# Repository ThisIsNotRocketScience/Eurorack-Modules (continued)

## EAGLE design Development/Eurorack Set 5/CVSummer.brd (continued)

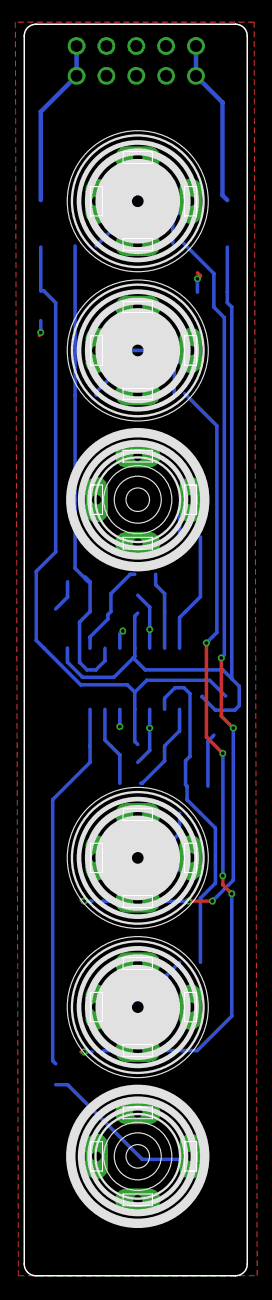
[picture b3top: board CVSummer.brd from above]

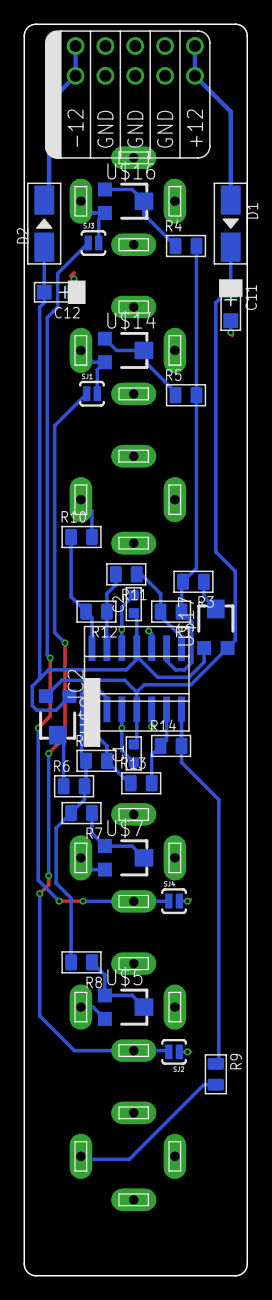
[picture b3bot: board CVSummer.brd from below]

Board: 2 copper layers, 19.0 x 106.5 mm, 39 parts (32 on the bottom side), 27 nets.

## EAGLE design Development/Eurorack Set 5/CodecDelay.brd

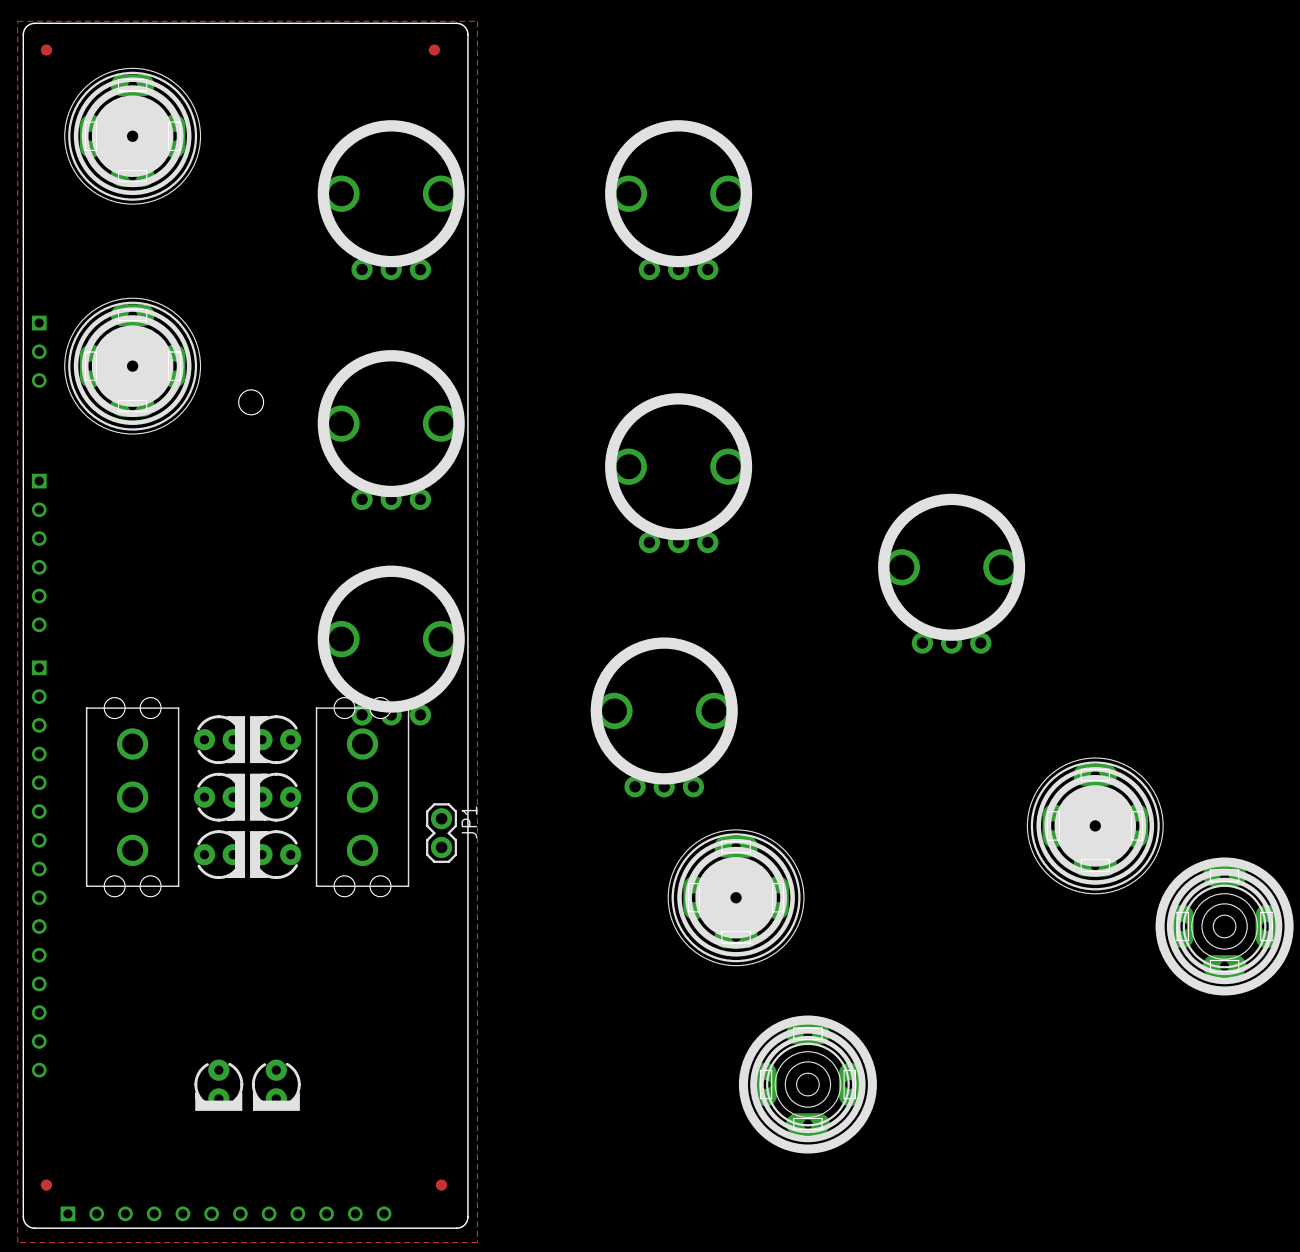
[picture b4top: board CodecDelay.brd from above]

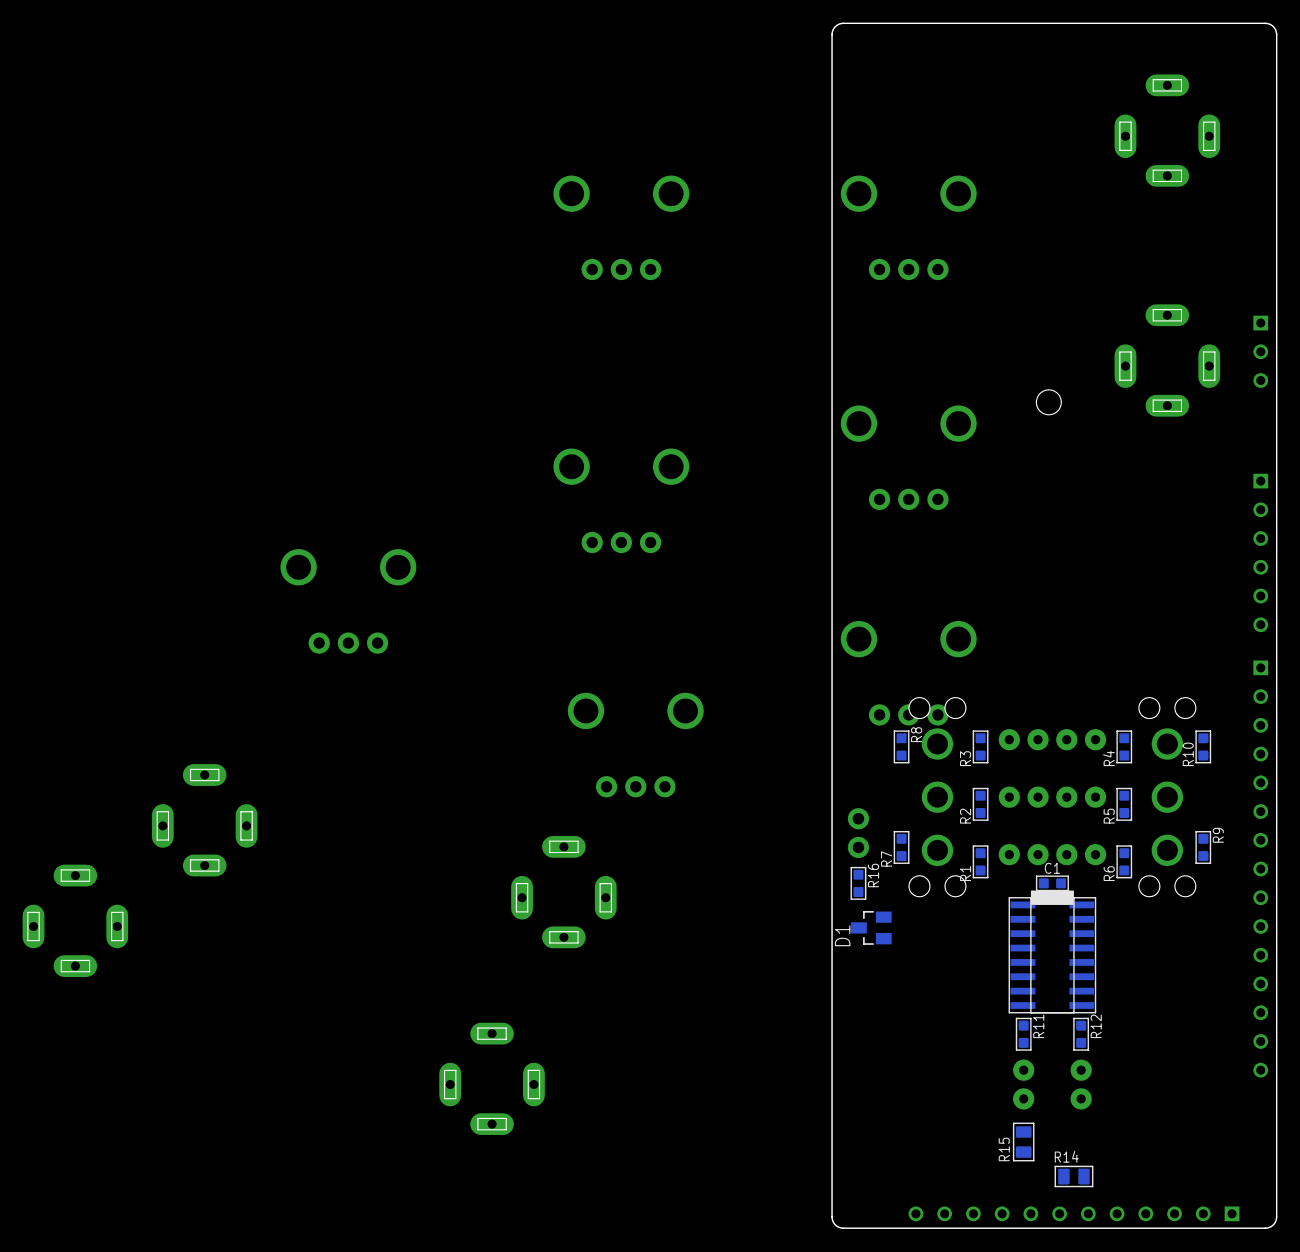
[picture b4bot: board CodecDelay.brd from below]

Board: 2 copper layers, 39.3 x 106.5 mm, 48 parts (18 on the bottom side), 34 nets, no tracks yet.

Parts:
C1: 100nF; C0603
D1: BAS70-04; SOT23
IC2: IC_74HC595-SOIC-16; SOIC-16
JP1: M02PTH; 1X02
LED1, LED2, LED3, LED4, LED5, LED6, LED7, LED8: WHITE; LED3MM
R1, R2, R3, R4, R5, R6, R11, R12: 50; R0603
R7, R8, R9, R10: 10k; R0603
R14, R15: 300; C0805
R16: 300; R0603
U$1: MCUBOARD; MCUBASEBOARD
U$2: EURORACK_PCB8HP; EURORACK8HPPCB
U$3: CV 1; 3.5MM-JACK-SWITCH-13MM-INPUT
U$4: CV 2; 3.5MM-JACK-SWITCH-13MM-INPUT
U$5: IN 1; 3.5MM-JACK-SWITCH-13MM-INPUT
U$6: IN 2; 3.5MM-JACK-SWITCH-13MM-INPUT
U$7: OUT 1; 3.5MM-JACK-SWITCH-13MM-OUTPUT
U$8: OUT 2; 3.5MM-JACK-SWITCH-13MM-OUTPUT
U$9, U$10, U$11, U$14, U$19, U$20, U$21: DRIVE; OG-POTS_ALPS_POT_VERTICAL
U$12, U$13: ONOFFON; MULTICOMP1MS-ONOFFON
U$15, U$16, U$17, U$18: FIDUCIAL; FIDUCIAL_1MM

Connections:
3.3V: C1.2, D1.2, IC2.10, IC2.16, R7.1, R8.1, R9.1, R10.1, U$1.3.3V, U$9.P$3, U$10.P$3, U$11.P$3, U$14.P$3, U$19.P$3, U$20.P$3, U$21.P$3
GND: C1.1, D1.1, IC2.8, IC2.13, JP1.1, LED1.K, LED2.K, LED3.K, LED4.K, LED5.K, LED6.K, LED7.K, LED8.K, U$1.GND@1, U$1.GND@2, U$1.GND@4, U$1.GND@5, U$1.GND@6, U$1.GND@7, U$1.GND@8, U$1.GND@9, U$1.GND_BUS, U$3.RING@3, U$3.SWITCH@3, U$4.RING@3, U$4.SWITCH@3, U$5.RING@3, U$5.SWITCH@3, U$6.RING@3, U$7.RING@3, U$8.RING@3, U$9.P$1, U$10.P$1, U$11.P$1, U$12.2, U$13.2, U$14.P$1, U$19.P$1, U$20.P$1, U$21.P$1
LEDB1: IC2.15, R6.1
LEDB2: IC2.1, R5.1
LEDB3: IC2.2, R4.1
LEDB4: IC2.3, R3.1
LEDB5: IC2.4, R2.1
LEDB6: IC2.5, R1.1
LEDB7: IC2.6, R12.1
LEDB8: IC2.7, R11.1
LEDCLOCK: IC2.11, U$1.TX/D7
LEDDAT: IC2.14, U$1.ADC4
LEDLATCH: IC2.12, U$1.ADC7
MODE1_A: R7.2, U$1.ADC13, U$12.1
MODE1_B: R8.2, U$1.RX/B16, U$12.3
MODE2_A: R9.2, U$1.TX/B17, U$13.1
MODE2_B: R10.2, U$1.ADC14, U$13.3
unnamed: U$1.IN_L, U$5.TIP@3
unnamed: U$1.IN_R, U$6.TIP@3
unnamed: U$1.CV_MIX1, U$3.TIP@3
unnamed: R14.2, U$7.TIP@3
unnamed: R15.2, U$6.SWITCH@3, U$8.TIP@3
unnamed: LED1.A, R6.2
unnamed: LED2.A, R5.2
unnamed: R14.1, U$1.OUT_L
unnamed: R15.1, U$1.OUT_R
unnamed: D1.3, R16.2, U$1.OUT_DAC
unnamed: LED3.A, R4.2
unnamed: LED4.A, R3.2
unnamed: LED5.A, R2.2
unnamed: LED6.A, R1.2
unnamed: LED7.A, R12.2
unnamed: LED8.A, R11.2
unnamed: JP1.2, R16.1

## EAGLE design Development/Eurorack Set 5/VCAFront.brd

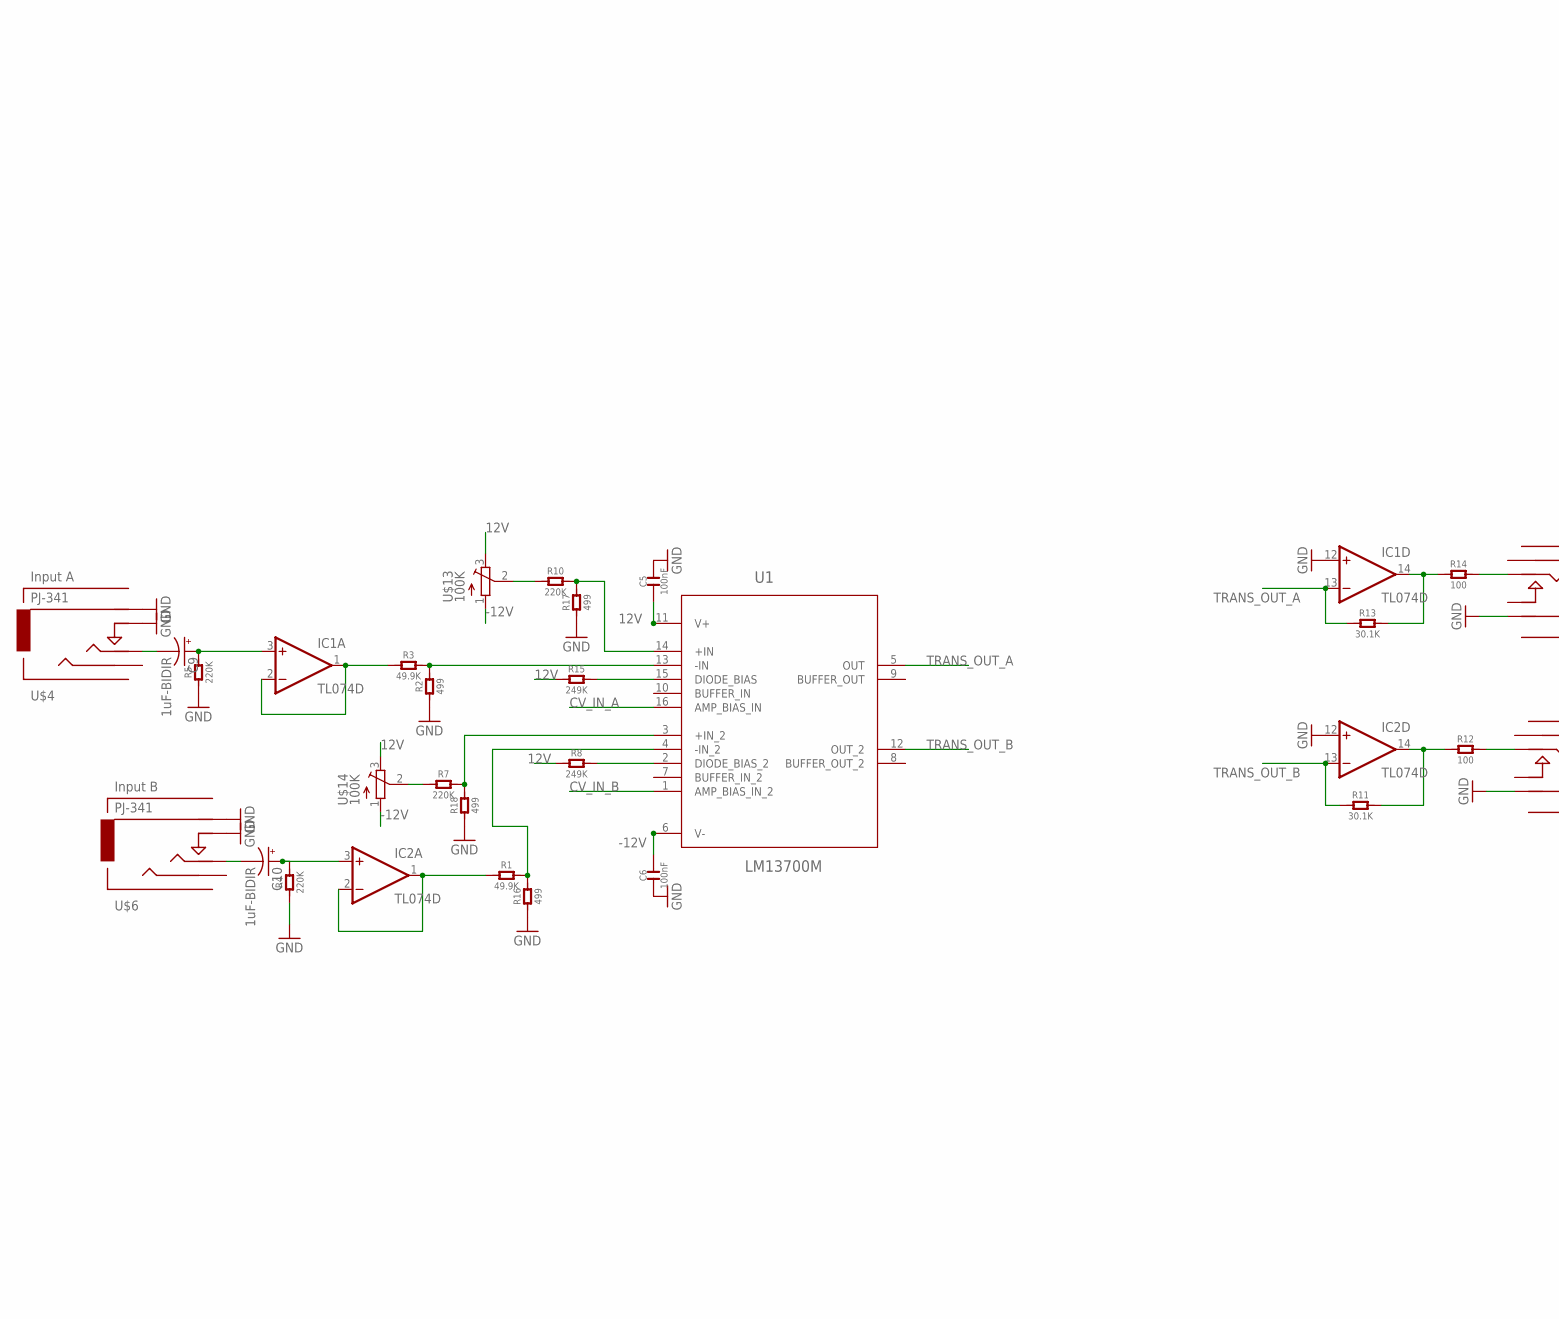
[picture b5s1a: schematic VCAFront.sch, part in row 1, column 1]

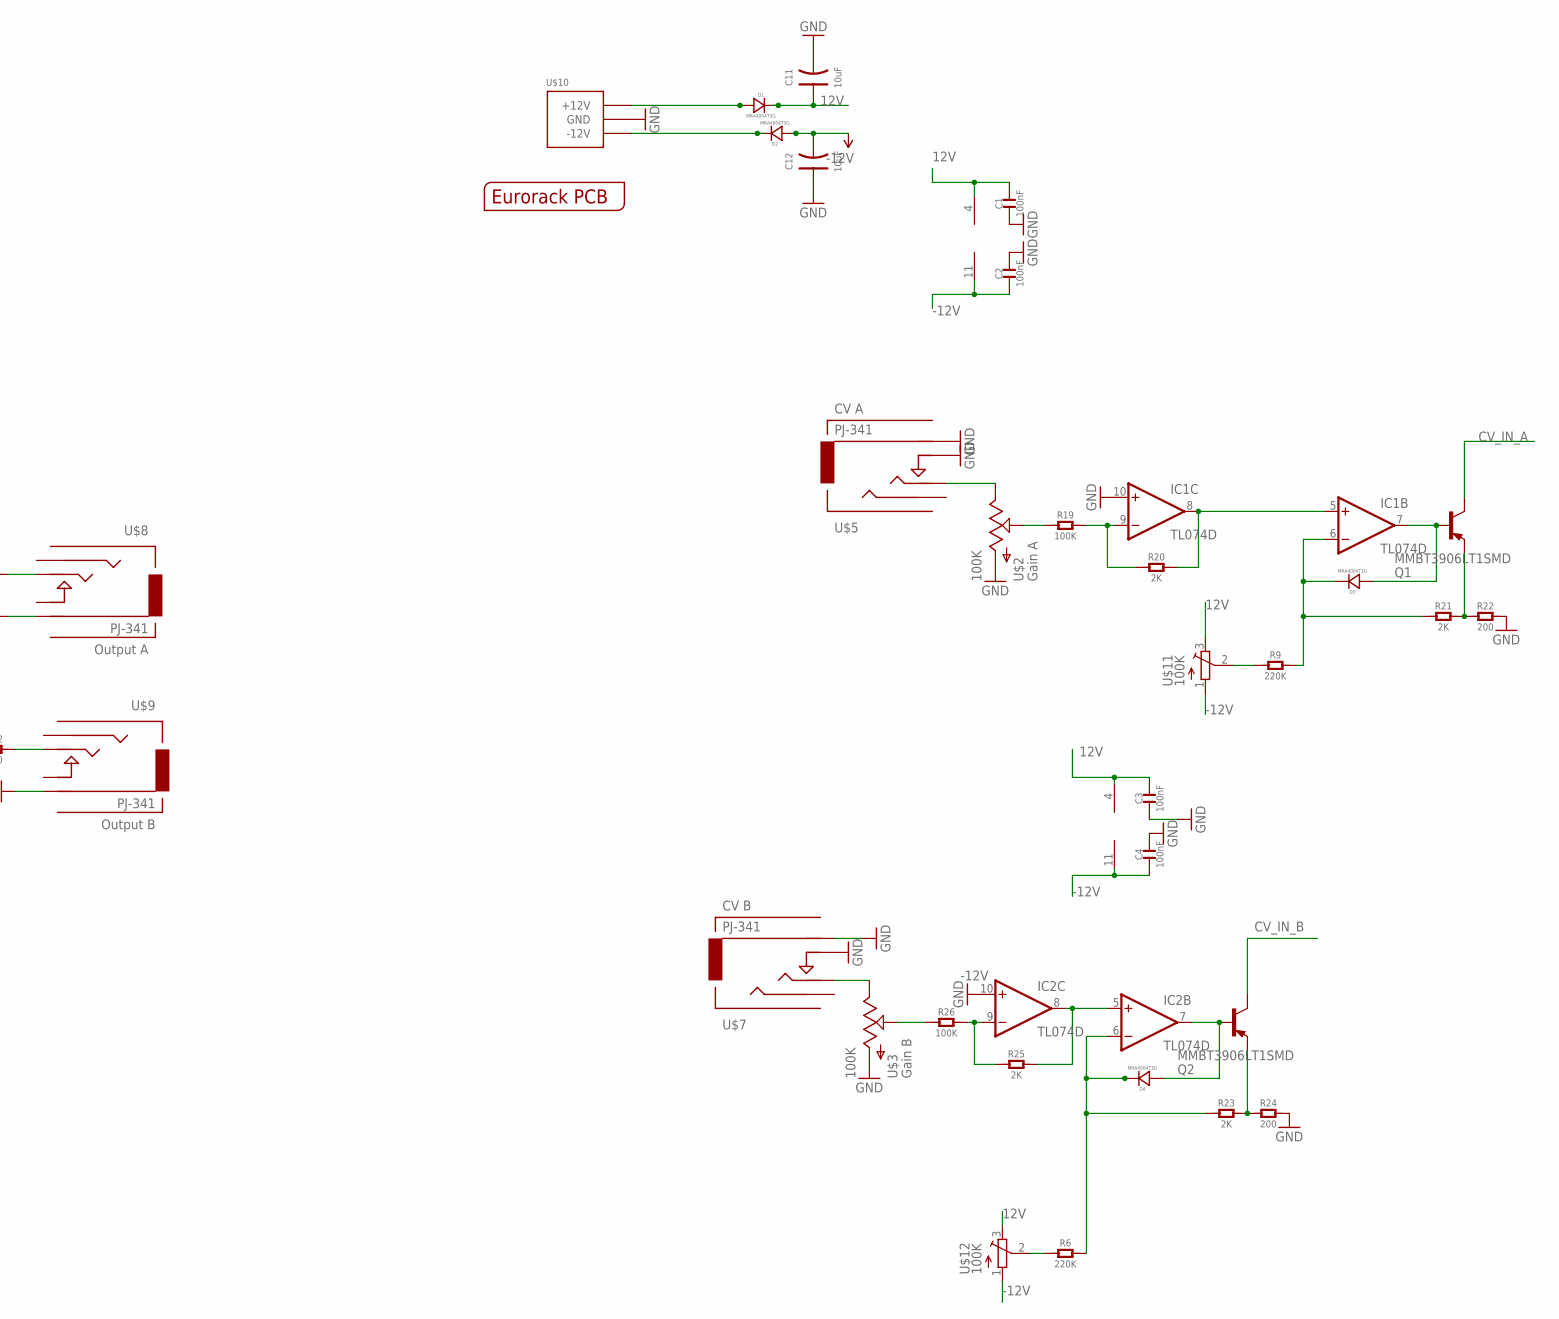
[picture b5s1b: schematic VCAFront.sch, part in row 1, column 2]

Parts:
C1, C2, C3, C4, C5, C6: 100nF; C0603
C9, C10: 1uF-BIDIR; 153CLV-0505
C11, C12: 10uF; AVX-A
D1, D2, D3, D4: MRA4004T3G; DO-214AC; MPN US1G-E3/5AT
IC1, IC2: TL074D; SO14
Q1, Q2: MMBT3906LT1SMD; SOT23-BEC
R1, R3: 49.9K; C0805
R2, R16, R17, R18: 499; C0805
R4, R5, R6, R7, R9, R10: 220K; C0805
R8, R15: 249K; C0805
R11, R13: 30.1K; C0805
R12, R14: 100; C0805
R19, R26: 100K; C0805
R20, R21, R23, R25: 2K; C0805
R22, R24: 200; C0805
U1: LM13700M; SOIC127P620X175-16N
U$1: EURORACK_PCB4HP; EURORACK4HPPCB
U$2, U$3: 100K; OG-POTS_ALPS_POT_VERTICAL
U$4, U$5, U$6, U$7: PJ-341; 3.5MM-JACK-SWITCH-13MM-INPUT
U$8, U$9: PJ-341; 3.5MM-JACK-SWITCH-13MM-OUTPUT
U$10: POWER_SIMPLE10; POWER_10
U$11, U$12, U$13, U$14: 100K; TC33X

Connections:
12V: C1.2, C3.2, C5.1, C11.+ (1), D1.2 (-), IC1.4 (V+), IC2.4 (V+), R8.1, R15.1, U1.11 (V+), U$11.3 (E), U$12.3 (E), U$13.3 (E), U$14.3 (E)
-12V: C2.1, C4.1, C6.2, C12.- (2), D2.1 (+), IC1.11 (V-), IC2.11 (V-), U1.6 (V-), U$11.1 (A), U$12.1 (A), U$13.1 (A), U$14.1 (A)
CV_IN_A: Q1.C, U1.16 (AMP_BIAS_IN)
CV_IN_B: Q2.C, U1.1 (AMP_BIAS_IN_2)
GND: C1.1, C2.2, C3.1, C4.2, C5.2, C6.1, C11.- (2), C12.+ (1), IC1.10 (+IN), IC1.12 (+IN), IC2.10 (+IN), IC2.12 (+IN), R2.1, R4.1, R5.1, R16.1, R17.1, R18.1, R22.2, R24.2, U$2.P$3 (A), U$3.P$3 (A), U$4.RING@3 (RING), U$4.SWITCH@3 (SWITCH), U$5.RING@3 (RING), U$5.SWITCH@3 (SWITCH), U$6.RING@3 (RING), U$6.SWITCH@3 (SWITCH), U$7.RING@3 (RING), U$7.SWITCH@3 (SWITCH), U$8.RING@3 (RING), U$9.RING@3 (RING), U$10.3 (GND), U$10.4 (GND), U$10.5 (GND), U$10.6 (GND), U$10.7 (GND), U$10.8 (GND)
unnamed: R14.2, U$8.TIP@3 (TIP)
unnamed: IC1.14 (OUT), R13.2, R14.1
unnamed: R8.2, U1.2 (DIODE_BIAS_2)
unnamed: R15.2, U1.15 (DIODE_BIAS)
unnamed: R12.2, U$9.TIP@3 (TIP)
unnamed: IC2.14 (OUT), R11.2, R12.1
unnamed: R19.1, U$2.P$2 (S)
unnamed: R10.1, U$13.2 (S)
unnamed: R9.1, U$11.2 (S)
unnamed: R7.1, U$14.2 (S)
unnamed: R6.1, U$12.2 (S)
unnamed: C9.-, U$4.TIP@3 (TIP)
unnamed: C10.-, U$6.TIP@3 (TIP)
unnamed: C9.+, IC1.3 (+IN), R5.2
unnamed: C10.+, IC2.3 (+IN), R4.2
unnamed: IC1.1 (OUT), IC1.2 (-IN), R3.1
unnamed: IC2.1 (OUT), IC2.2 (-IN), R1.1
unnamed: R2.2, R3.2, U1.13 (-IN)
unnamed: R1.2, R16.2, U1.4 (-IN_2)
unnamed: R10.2, R17.2, U1.14 (+IN)
unnamed: U$3.P$1 (E), U$7.TIP@3 (TIP)
unnamed: R7.2, R18.2, U1.3 (+IN_2)
unnamed: U$2.P$1 (E), U$5.TIP@3 (TIP)
unnamed: IC1.9 (-IN), R19.2, R20.1
unnamed: IC1.5 (+IN), IC1.8 (OUT), R20.2
unnamed: D3.2 (-), IC1.6 (-IN), R9.2, R21.1
unnamed: D1.1 (+), U$10.9 (+12V), U$10.10 (+12V)
unnamed: D3.1 (+), IC1.7 (OUT), Q1.B
unnamed: Q1.E, R21.2, R22.1
unnamed: D4.2 (-), IC2.6 (-IN), R6.2, R23.1
unnamed: D4.1 (+), IC2.7 (OUT), Q2.B
unnamed: Q2.E, R23.2, R24.1
unnamed: IC2.5 (+IN), IC2.8 (OUT), R25.2
unnamed: R26.1, U$3.P$2 (S)
unnamed: IC2.9 (-IN), R25.1, R26.2
unnamed: D2.2 (-), U$10.1 (-12V), U$10.2 (-12V)
TRANS_OUT_A: IC1.13 (-IN), R13.1, U1.5 (OUT)
TRANS_OUT_B: IC2.13 (-IN), R11.1, U1.12 (OUT_2)

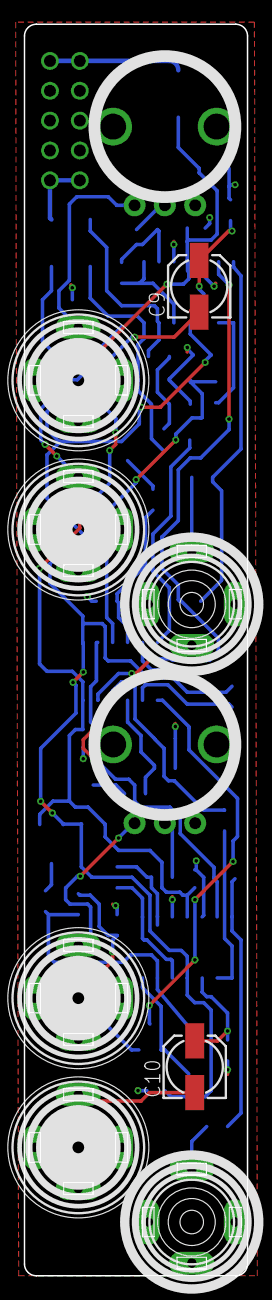
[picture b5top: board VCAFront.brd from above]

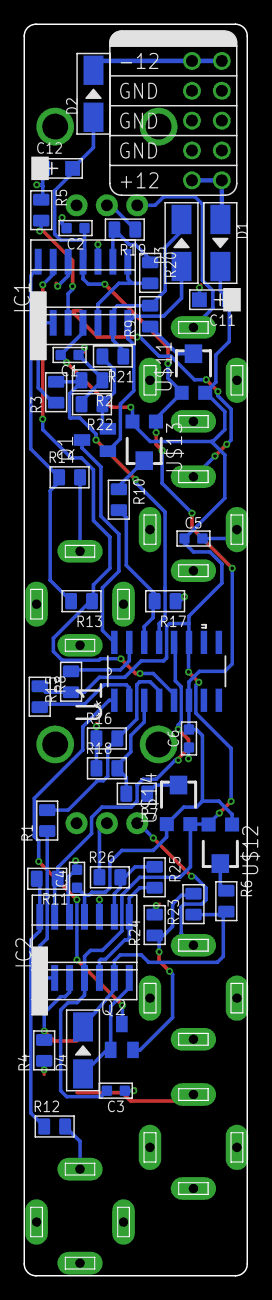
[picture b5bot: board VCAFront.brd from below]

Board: 2 copper layers, 19.0 x 106.5 mm, 59 parts (48 on the bottom side), 43 nets.

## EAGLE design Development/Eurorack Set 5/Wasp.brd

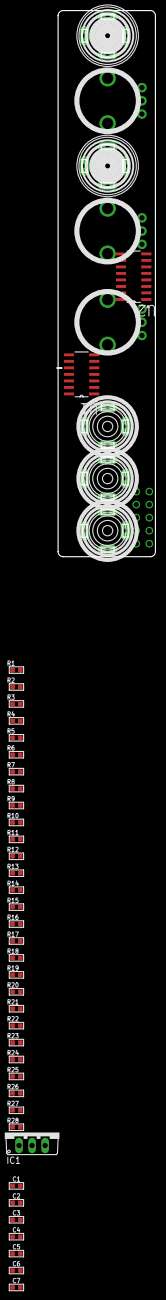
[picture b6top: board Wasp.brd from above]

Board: 2 copper layers, 19.0 x 106.5 mm, 48 parts (1 on the bottom side), 6 nets, no tracks yet.

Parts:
C1, C2, C3, C4, C5, C6, C7: C0603
IC1: 7805TV; TO220V
R1, R2, R3: 33K; R0603
R4, R5, R6: 100K; R0603
R7, R8, R9, R10, R11, R12, R13, R14, R15, R16, R17, R18, R19, R20, R21, R22, R23, R24, R25, R26, R27, R28: R0603
U1: CD4069UBM; SOIC127P600X175-14N
U2: LM13700M; SOIC127P620X175-16N
U$1: EURORACK_PCB4HP; EURORACK4HPPCB
U$2: 50K; OG-POTS_ALPS_POT_VERTICAL
U$3, U$4: OG-POTS_ALPS_POT_VERTICAL
U$5, U$6: PJ-341; 3.5MM-JACK-SWITCH-13MM-INPUT
U$7, U$8, U$9: PJ-341; 3.5MM-JACK-SWITCH-13MM-OUTPUT
U$10: POWER_SIMPLE10; POWER_10

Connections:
5V: C7.2, IC1.3
GND: IC1.2, U1.7, U2.6, U$2.P$3, U$5.RING@3, U$5.SWITCH@3, U$10.3, U$10.4, U$10.5, U$10.6, U$10.7, U$10.8
unnamed: R1.1, U$2.P$2
unnamed: U$2.P$1, U$5.TIP@3
unnamed: C6.2, IC1.1, U$10.9, U$10.10
unnamed: C1.1, R1.2
